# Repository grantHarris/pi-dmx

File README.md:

# pi-dmx
Isolated DMX shield with buffered SPI out for the Raspberry Pi

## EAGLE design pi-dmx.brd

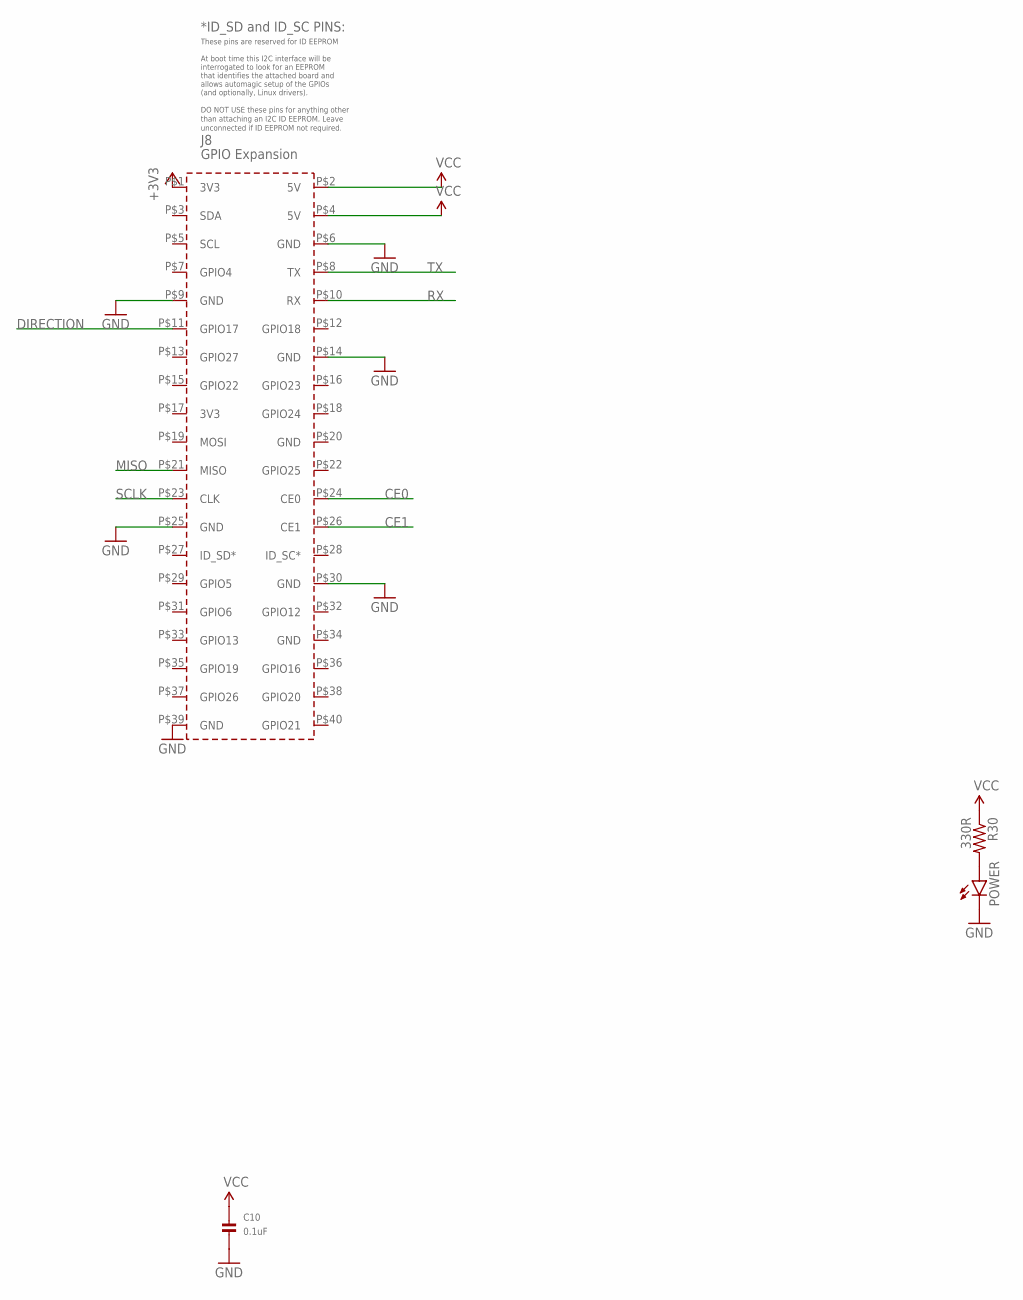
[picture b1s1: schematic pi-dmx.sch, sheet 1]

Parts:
C10: 0.1uF; 0805
PCB1: RPI2
POWER: LED1206; LED-1206
R30: 330R; 0603-RES

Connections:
+3V3: PCB1.P$1 (3V3); also elsewhere on the board
CE0: PCB1.P$24 (CE0); also elsewhere on the board
CE1: PCB1.P$26 (CE1); also elsewhere on the board
DIRECTION: PCB1.P$11 (GPIO17); also elsewhere on the board
GND: C10.2, PCB1.P$6 (GND), PCB1.P$9 (GND), PCB1.P$14 (GND), PCB1.P$25 (GND), PCB1.P$30 (GND), PCB1.P$39 (GND), POWER.C; also elsewhere on the board
MISO: PCB1.P$21 (MISO); also elsewhere on the board
unnamed: POWER.A, R30.2
RX: PCB1.P$10 (RX); also elsewhere on the board
SCLK: PCB1.P$23 (CLK); also elsewhere on the board
TX: PCB1.P$8 (TX); also elsewhere on the board
VCC: C10.1, PCB1.P$2 (5V), PCB1.P$4 (5V), R30.1; also elsewhere on the board

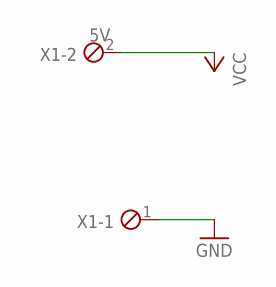
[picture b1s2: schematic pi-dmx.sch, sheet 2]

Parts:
X1: 5V; 2POL254

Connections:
GND: X1.1; also elsewhere on the board
VCC: X1.2; also elsewhere on the board

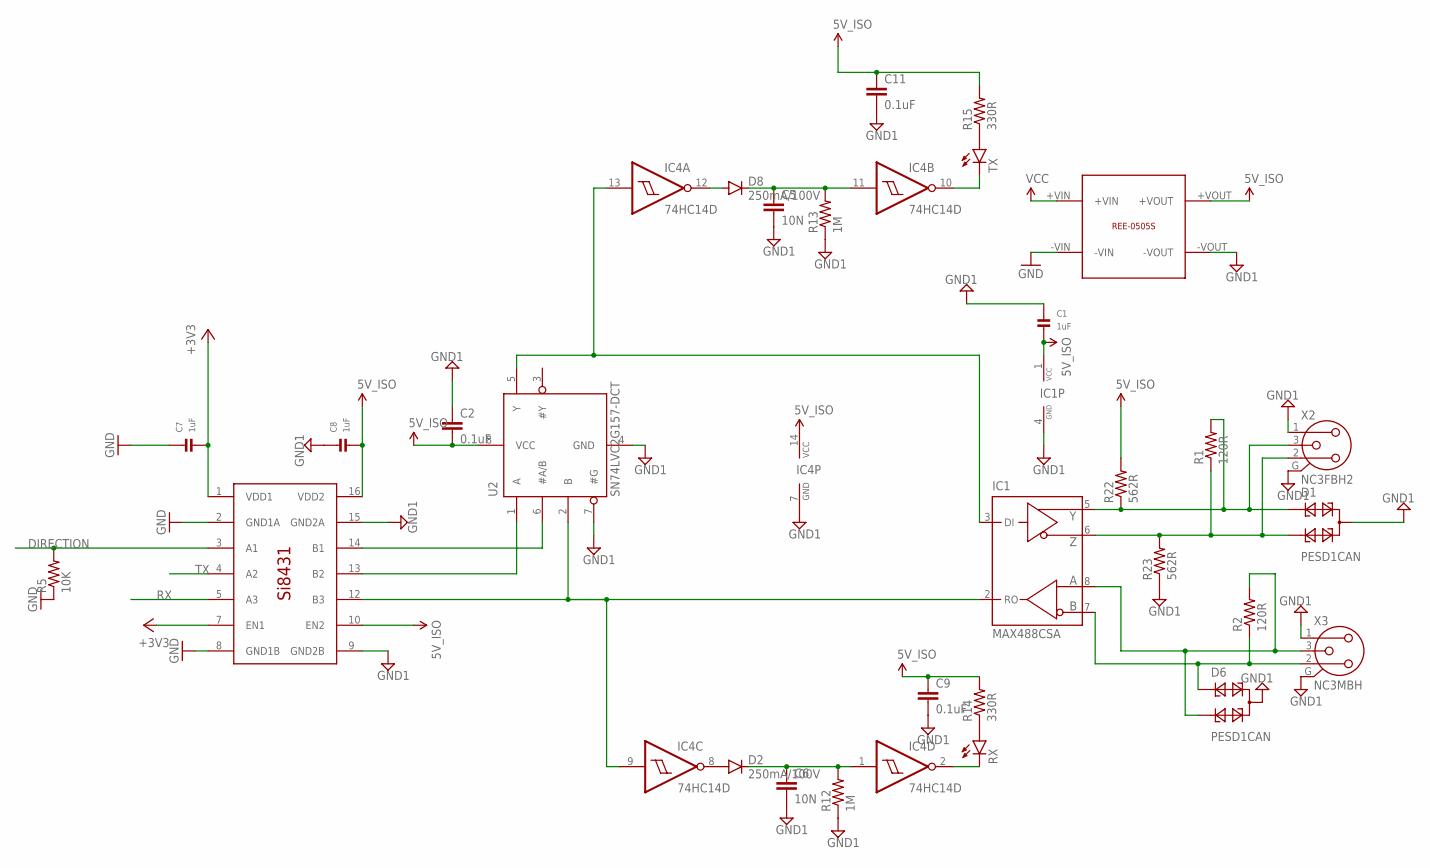
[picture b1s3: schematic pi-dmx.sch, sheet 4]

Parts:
C1, C7, C8: 1uF; 0805
C2, C9, C11: 0.1uF; 0603-CAP
C5, C6: 10N; 0603-CAP
D1, D6: PESD1CAN; SOT23
D2, D8: 250mA/100V; SOD-323
IC1: MAX488CSA; SO08
IC4: 74HC14D; SO14
R1, R2: 120R; 1206
R5: 10K; 0603-RES
R12, R13: 1M; 0603-RES
R14, R15: 330R; 0603-RES
R22, R23: 562R; 0603-RES
RX: LED1206; LED-1206
TX: LED1206; LED-1206
U2: SN74LVC2G157-DCT; SSOP8
U$6: REE-0505S
U$8: SI8431; SO16
X2: NC3FBH2
X3: NC3MBH

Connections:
5V: C1.2, C2.2, C8.2, C9.1, C11.1, IC1.1 (VCC), IC4.14 (VCC), R14.2, R15.2, R22.2, U2.8 (VCC), U$6.+VOUT, U$8.10 (EN2), U$8.16 (VDD2)
+3V3: C7.2, U$8.1 (VDD1), U$8.7 (EN1); also elsewhere on the board
DIRECTION: R5.2, U$8.3 (A1); also elsewhere on the board
GND: C7.1, R5.1, U$6.-VIN, U$8.2 (GND1A), U$8.8 (GND1B); also elsewhere on the board
GND1: C1.1, C2.1, C5.2, C6.2, C8.1, C9.2, C11.2, D1.3, D6.3, IC1.4 (GND), IC4.7 (GND), R12.1, R13.1, R23.1, U2.4 (GND), U2.7 (#G), U$6.-VOUT, U$8.9 (GND2B), U$8.15 (GND2A), X2.1, X2.G, X3.1, X3.G
unnamed: D2.A, IC4.8 (O)
unnamed: D8.A, IC4.12 (O)
unnamed: D6.1, IC1.7 (B), R2.1, X3.2
unnamed: U2.6 (#A/B), U$8.14 (B1)
unnamed: U2.1 (A), U$8.13 (B2)
unnamed: D6.2, IC1.8 (A), R2.2, X3.3
unnamed: IC1.3 (DI), IC4.13 (I), U2.5 (Y)
unnamed: C5.1, D8.C, IC4.11 (I), R13.2
unnamed: C6.1, D2.C, IC4.1 (I), R12.2
unnamed: D1.1, IC1.5 (Y), R1.2, R22.1, X2.3
unnamed: D1.2, IC1.6 (Z), R1.1, R23.2, X2.2
unnamed: R14.1, RX.A
unnamed: IC4.2 (O), RX.C
unnamed: R15.1, TX.A
unnamed: IC4.10 (O), TX.C
unnamed: IC1.2 (RO), IC4.9 (I), U2.2 (B), U$8.12 (B3)
RX: U$8.5 (A3); also elsewhere on the board
TX: U$8.4 (A2); also elsewhere on the board
VCC: U$6.+VIN; also elsewhere on the board

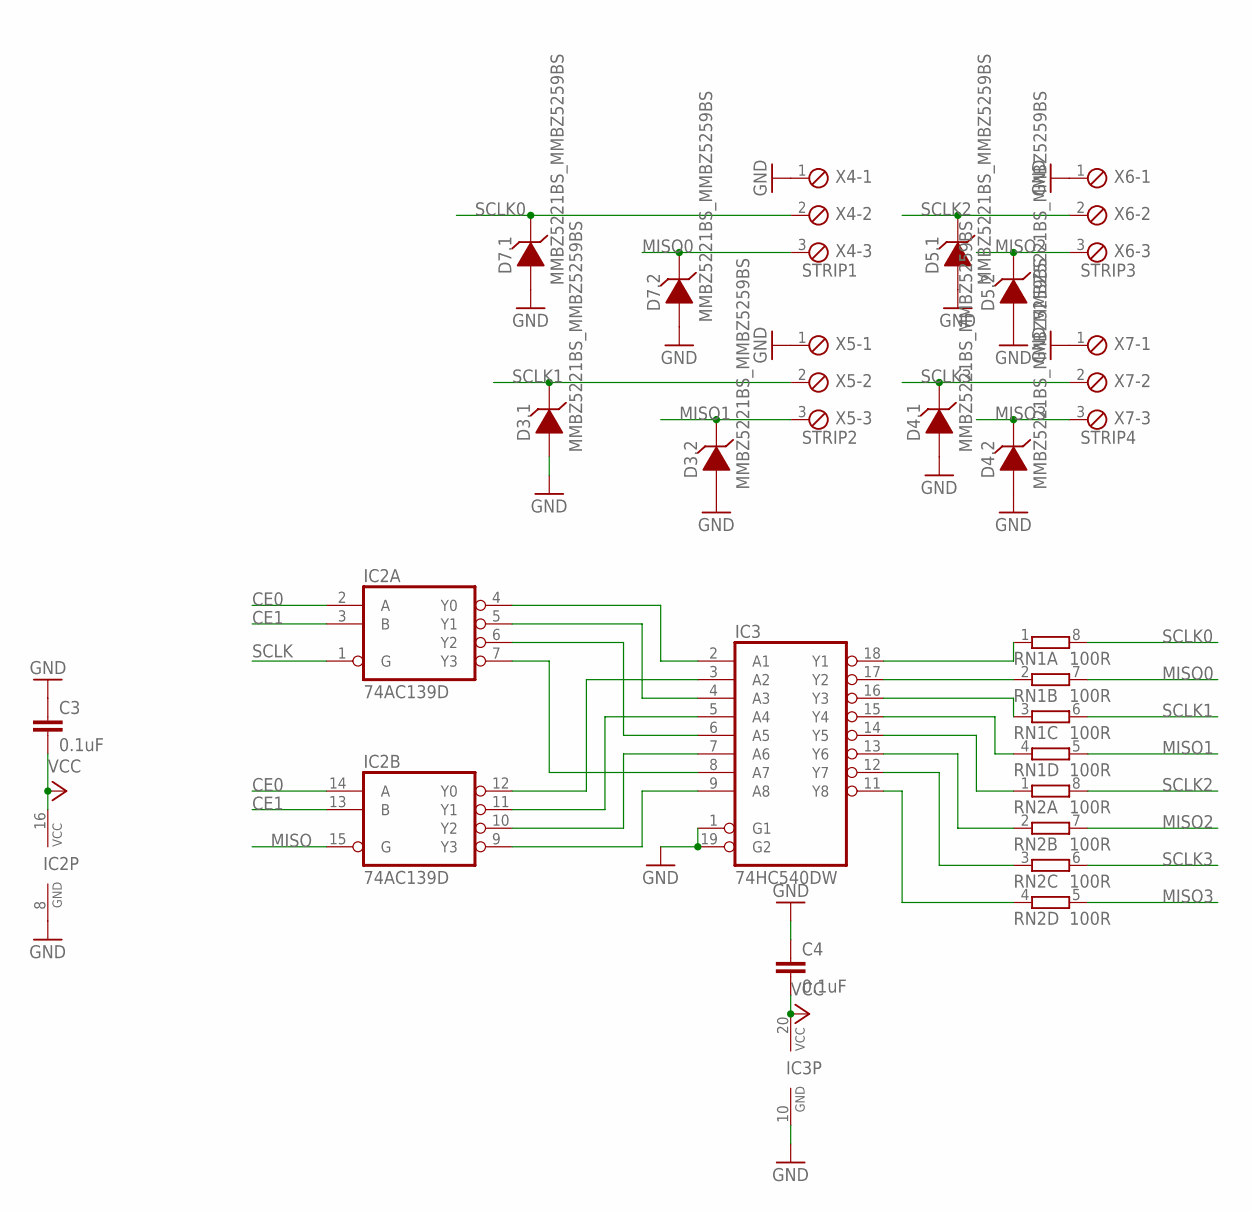
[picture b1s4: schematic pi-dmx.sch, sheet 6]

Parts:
C3, C4: 0.1uF; 0603-CAP
D3, D4, D5, D7: MMBZ5221BS_MMBZ5259BS; SOT363_PHILIPS
IC2: 74AC139D; SO16
IC3: 74HC540DW; SO20W
RN1, RN2: 100R; EXBS8V
X4: STRIP1; 3POL254
X5: STRIP2; 3POL254
X6: STRIP3; 3POL254
X7: STRIP4; 3POL254

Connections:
CE0: IC2.2 (A), IC2.14 (A); also elsewhere on the board
CE1: IC2.3 (B), IC2.13 (B); also elsewhere on the board
GND: C3.1, C4.1, D3.1 (A), D3.4 (A), D4.1 (A), D4.4 (A), D5.1 (A), D5.4 (A), D7.1 (A), D7.4 (A), IC2.8 (GND), IC3.1 (G1), IC3.10 (GND), IC3.19 (G2), X4.1, X5.1, X6.1, X7.1; also elsewhere on the board
MISO: IC2.15 (G); also elsewhere on the board
MISO0: D7.3 (C), RN1.7 (2), X4.3
MISO1: D3.3 (C), RN1.5 (2), X5.3
MISO2: D5.3 (C), RN2.7 (2), X6.3
MISO3: D4.3 (C), RN2.5 (2), X7.3
unnamed: IC3.17 (Y2), RN1.2 (1)
unnamed: IC3.18 (Y1), RN1.1
unnamed: IC3.16 (Y3), RN1.3 (1)
unnamed: IC3.15 (Y4), RN1.4 (1)
unnamed: IC2.4 (Y0), IC3.2 (A1)
unnamed: IC2.5 (Y1), IC3.4 (A3)
unnamed: IC2.6 (Y2), IC3.6 (A5)
unnamed: IC2.7 (Y3), IC3.8 (A7)
unnamed: IC2.12 (Y0), IC3.3 (A2)
unnamed: IC2.11 (Y1), IC3.5 (A4)
unnamed: IC2.10 (Y2), IC3.7 (A6)
unnamed: IC2.9 (Y3), IC3.9 (A8)
unnamed: IC3.14 (Y5), RN2.1
unnamed: IC3.13 (Y6), RN2.2 (1)
unnamed: IC3.12 (Y7), RN2.3 (1)
unnamed: IC3.11 (Y8), RN2.4 (1)
SCLK: IC2.1 (G); also elsewhere on the board
SCLK0: D7.6 (C), RN1.8 (2), X4.2
SCLK1: D3.6 (C), RN1.6 (2), X5.2
SCLK2: D5.6 (C), RN2.8 (2), X6.2
SCLK3: D4.6 (C), RN2.6 (2), X7.2
VCC: C3.2, C4.2, IC2.16 (VCC), IC3.20 (VCC); also elsewhere on the board

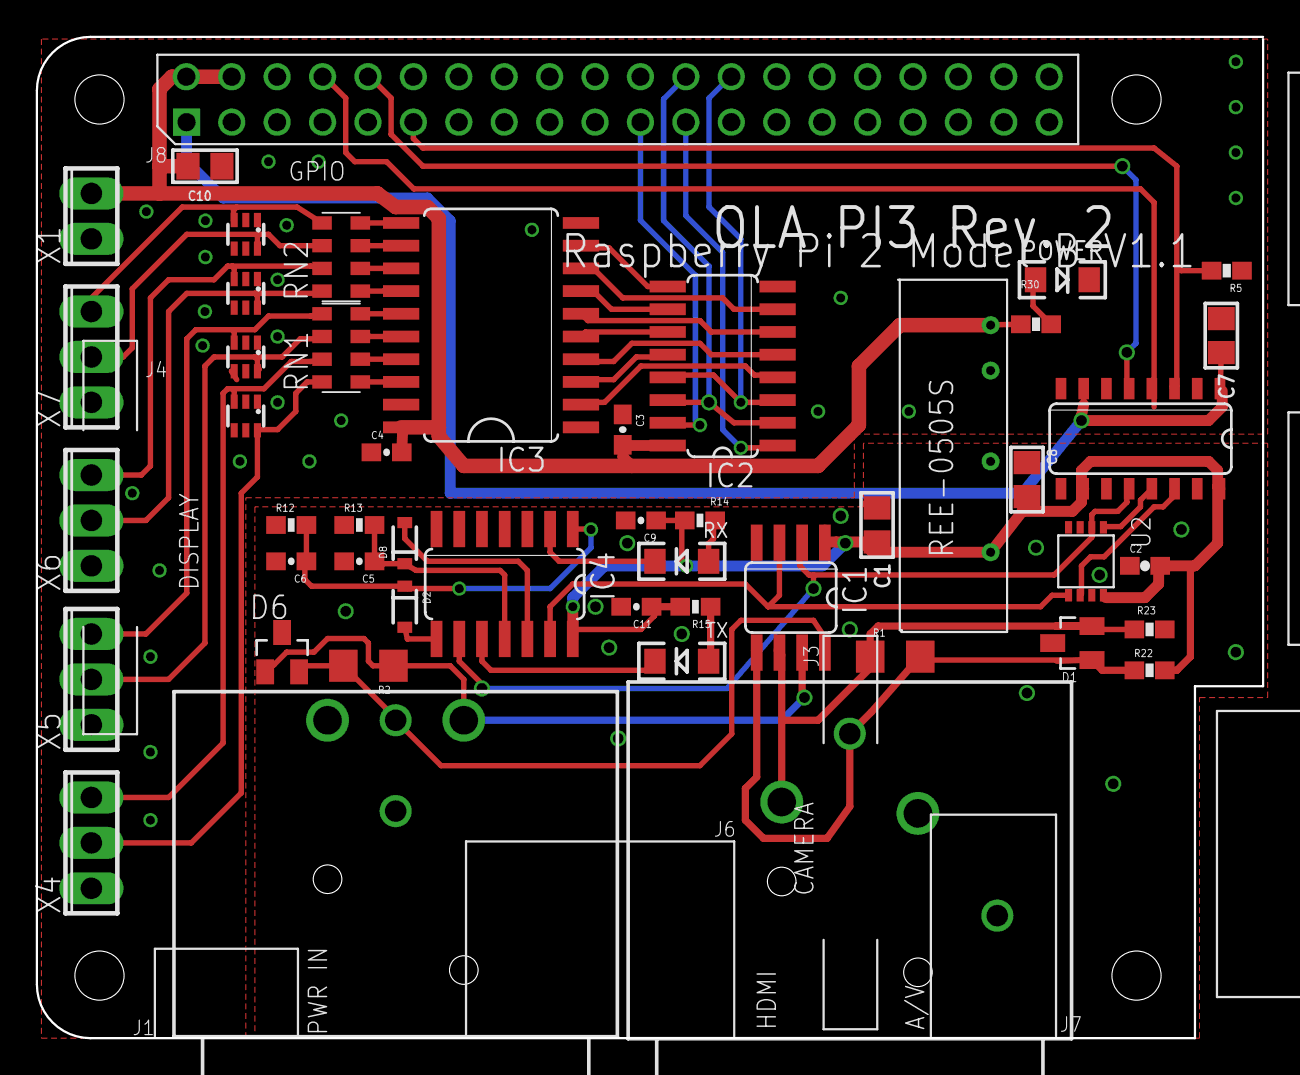
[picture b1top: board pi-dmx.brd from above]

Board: 2 copper layers, 68.6 x 56.0 mm, 49 parts (0 on the bottom side), 53 nets.

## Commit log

2016-05-08 Add schematic and board
2016-05-09 Labels cleaned up
2016-05-09 Added reset button and fixed connector layout
2016-07-06 Raspberry Pi 3 version
2016-07-16 Board mfg candidate

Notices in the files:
parts and their libraries:
microbuilder: This work is placed in the public domain, and may be freely used for commercial and non-commercial work with the following conditions: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
SparkFun-LED: Licensing: Creative Commons ShareAlike 4.0 International - https://creativecommons.org/licenses/by-sa/4.0
